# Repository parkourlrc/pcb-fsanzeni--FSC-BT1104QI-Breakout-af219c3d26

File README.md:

# Feasycom FSC-BT1104QI Breakout Board

An open-hardware breakout board designed for the Feasycom FSC-BT1104QI Bluetooth 5.4 dual-mode audio module.

This breakout board exposes the complete feature set and physical interface of the FSC-BT1104QI module. Rather than targeting standard breadboard layouts, the dual 32-pin header design breaks out all available module pins, making it an ideal core for integration into custom target boards, carrier systems, etc.

---

## Board Overview

### Front & Back Renders

| Board Front Layout | Board Rear Header Map |
| :---: | :---: |
|  |  |

---

## Key Hardware Features

- **Bluetooth Core**: Feasycom FSC-BT1104QI module supporting Bluetooth v5.4 dual-mode (Classic Bluetooth + LE Audio), preloaded with ASCII AT command modem firmware.
- **System Integration Design**: Engineered to break out all pins for clean integration onto parent/carrier PCBs.
- **USB Connectivity & Switching**: USB Type-C connector with an onboard high-bandwidth USB multiplexer (`U1`) allowing selection between direct USB communication with the Bluetooth module or serial debugging via an onboard USB-to-UART bridge.
- **Power Management**: Onboard low-noise 3.3V 600mA LDO regulator (`U3`) powering the module and peripheral logic from USB 5V.
- **Audio Routing**:
  - **Digital Audio**: Dedicated 6-pin header (`J6`) for 24-bit I2S / PCM digital audio interfaces.
  - **Analog Audio**: Dedicated 6-pin differential speaker output header (`J8`), multi-channel differential line inputs, and dual electret microphone input circuits with LC filtering.
- **Diagnostics & Testing**: Dedicated test point array (`TP1`–`TP9`) for probing power rails, reset lines, and RS-232 / UART hardware handshaking signals.

---

## Integrated Circuits

| Component Ref | Part Number | Functional Description | Key Electrical & Operating Capabilities | Datasheet Link |
| :--- | :--- | :--- | :--- | :--- |
| **U5** | **FSC-BT1104QI** | Bluetooth 5.4 Dual-Mode Audio Module (Qualcomm QCC3095 architecture, 240 MHz DSP, LE Audio, Classic BT) | - **Bluetooth Standard**: Bluetooth v5.4<br>- **Supply Voltage**: 3.3V (VDD_IO: 1.8V/3.3V)<br>- **Tx Power / Rx Sensitivity**: +10 dBm / -93 dBm<br>- **Audio Codecs**: aptX, aptX HD, aptX Adaptive, AAC, LDAC<br>- **Operating Temp**: -40°C to +85°C | [FSC-BT1104QI Datasheet](https://www.feasycom.com/product/fsc-bt1104qi/) |
| **U3** | **AP2112K-3.3** | CMOS Low Dropout (LDO) Linear Voltage Regulator | - **Input Voltage Range**: 2.5V to 6.0V<br>- **Output Voltage**: 3.3V fixed (±1.5% accuracy)<br>- **Max Output Current**: 600 mA<br>- **Dropout Voltage**: 250 mV typical at 600 mA<br>- **Features**: Enable control, current limit, thermal shutdown | [AP2112K-3.3 Datasheet](https://www.diodes.com/assets/Datasheets/AP2112.pdf) |
| **U4** | **CH340G** | USB to Serial / UART Interface Bridge Transceiver | - **USB Interface**: USB 2.0 Full-Speed compliant<br>- **Baud Rates**: 50 bps to 2 Mbps<br>- **Supply Voltage**: 3.3V or 5.0V operation<br>- **Signals**: Full modem signals (RTS, CTS, DTR, DSR, RI, DCD) | [CH340G Datasheet](https://cdn.sparkfun.com/datasheets/Dev/Arduino/Other/CH340DS1.PDF) |
| **U1** | **TS3USB30EDGSR** | High-Speed USB 2.0 (480 Mbps) 1:2 Multiplexer / Switch | - **Supply Voltage Range**: 1.8V to 4.3V<br>- **Bandwidth**: 900 MHz (-3 dB bandwidth)<br>- **ON-State Resistance**: 4.5 Ω typical<br>- **ESD Protection**: 8 kV HBM ESD performance | [TS3USB30EDGSR Datasheet](https://www.ti.com/product/TS3USB30E/part-details/TS3USB30EDGSR) |

---

## Pinout Definitions & Interface Maps

### 1. Right Header Connector `P1`

---

### 2. Left Header Connector `P2`

---

### 3. Digital Audio Header `J6` (I2S Connector)

---

### 4. Differential Speaker Header `J8`

---

### 5. Onboard Diagnostic Test Points (`TP1`–`TP9`)

---

## Jumpers & Configuration Switches

- **`J1` (`USB_SEL`)**:
  - **Bridge 1-2**: Route USB Type-C lines to **CH340G** USB-to-UART bridge.
  - **Bridge 2-3**: Route USB Type-C lines directly to the **FSC-BT1104QI** module.
- **`JP1` (`ENABLE`)**: Disconnect if feeding 3.3V from P1 or P2.
- **`SW1` (`POWER_ON` / `SYS_CTRL`)**: Momentary push button tied to `SYS_CTRL` (Pin 2 on FSC module) for powering on/off or waking the module from sleep modes.

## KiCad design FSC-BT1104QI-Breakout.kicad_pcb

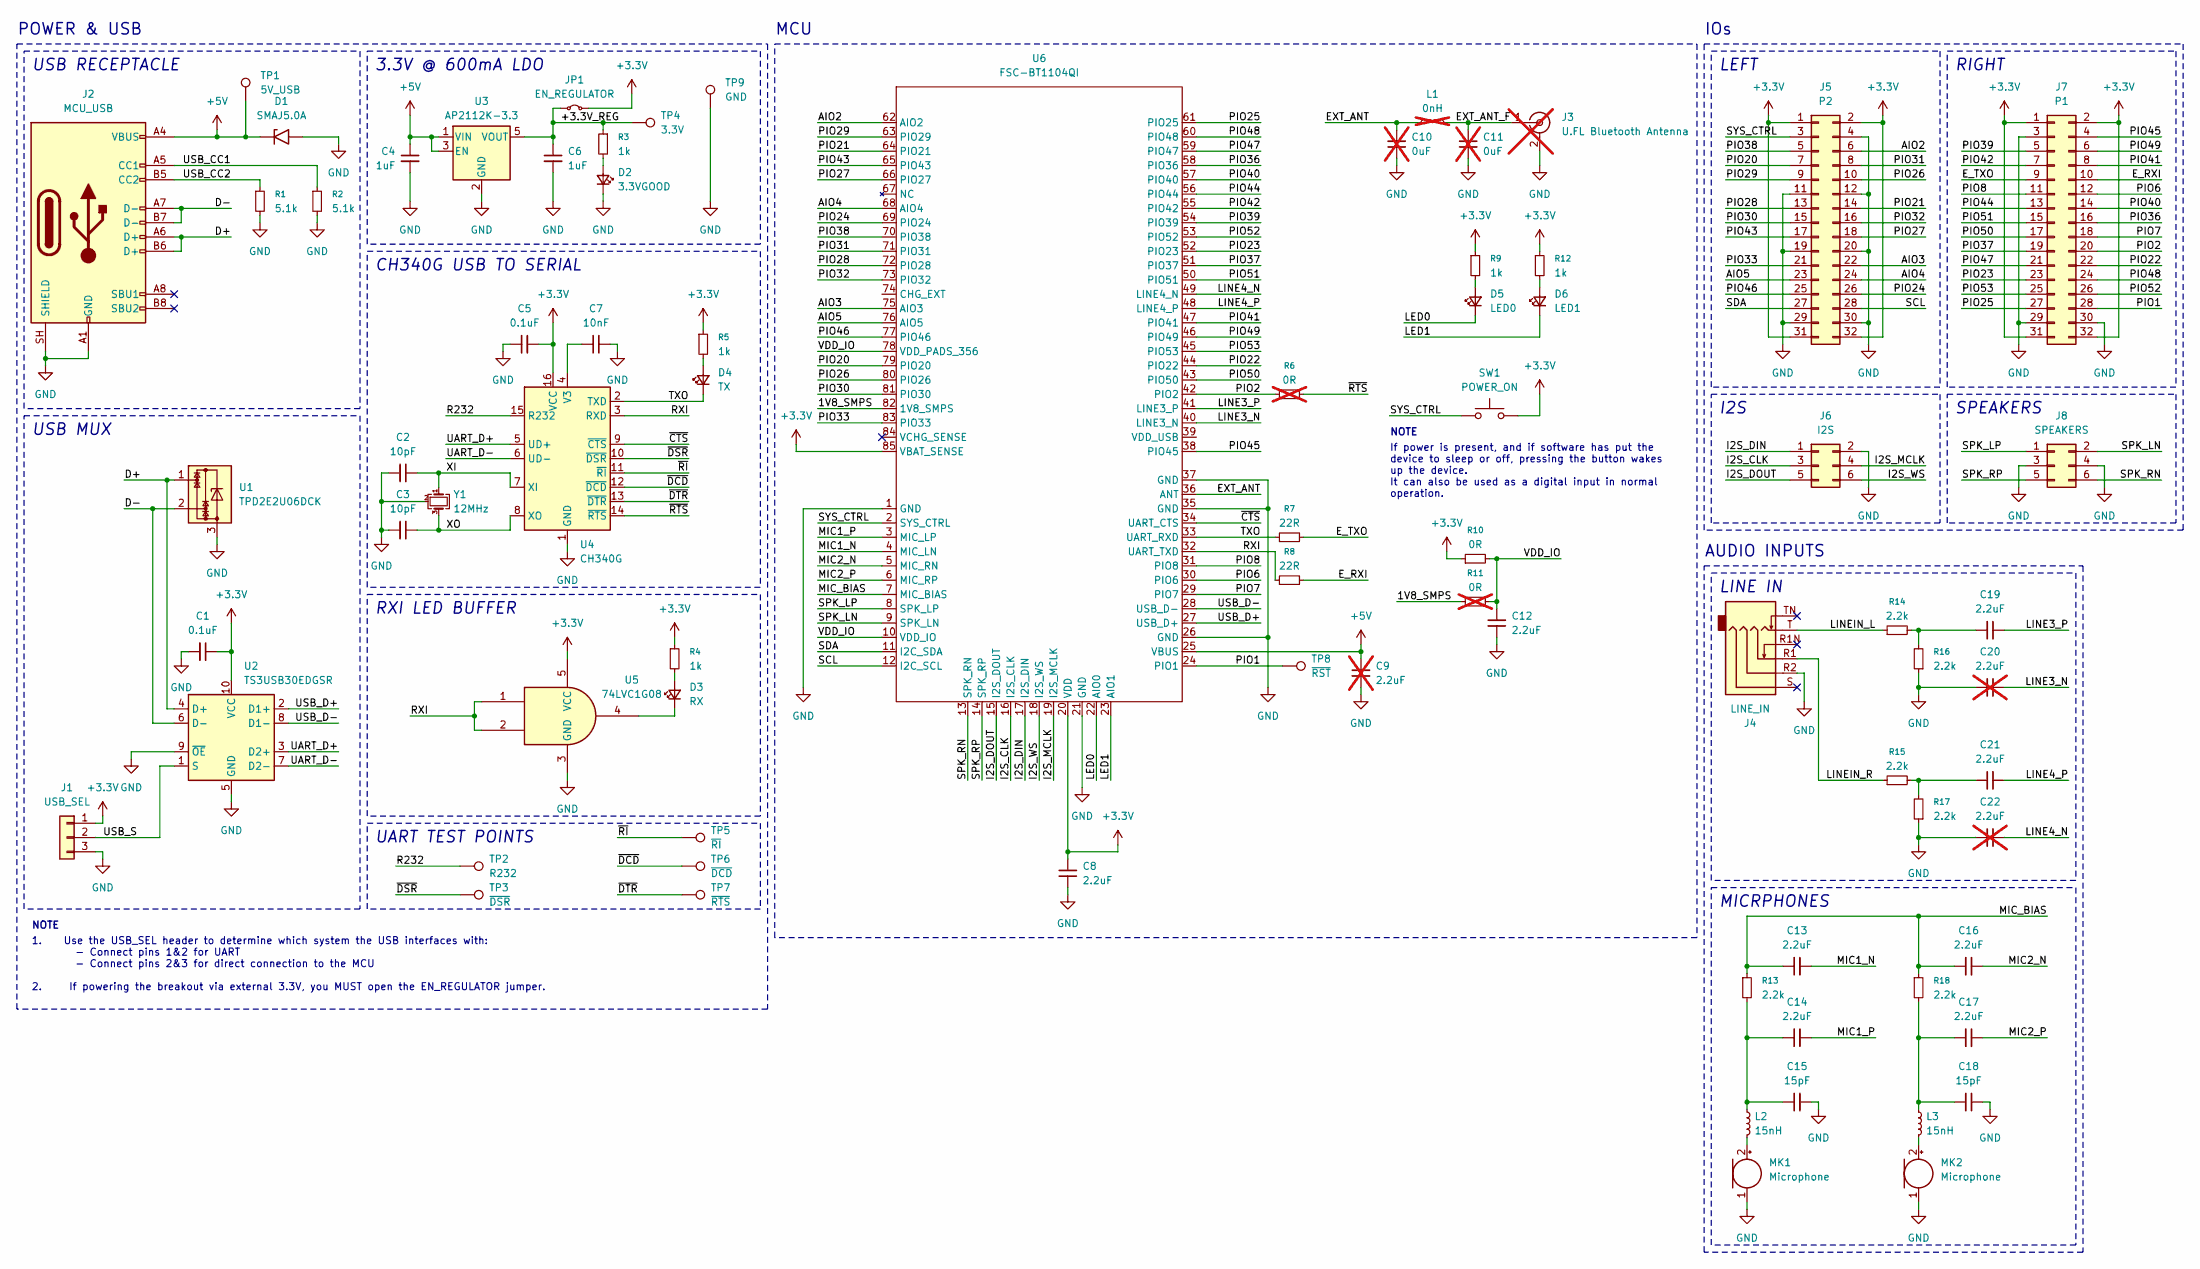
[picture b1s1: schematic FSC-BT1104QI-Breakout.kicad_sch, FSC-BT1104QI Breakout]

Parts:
C1, C5: 0.1uF; C_0603_1608Metric
C2, C3: 10pF; C_0603_1608Metric
C4, C6: 1uF; C_0805_2012Metric
C7: 10nF; C_0603_1608Metric
C8, C12, C13, C14, C16, C17, C19, C21: 2.2uF; C_0603_1608Metric
C9, C20, C22: 2.2uF; C_0603_1608Metric; not fitted
C10, C11: 0uF; C_0603_1608Metric; not fitted
C15, C18: 15pF; C_0603_1608Metric
D1: SMAJ5.0A; D_SMA
D2: 3.3VGOOD; LED_0603_1608Metric
D3: RX; LED_0603_1608Metric
D4: TX; LED_0603_1608Metric
D5: LED0; LED_0603_1608Metric
D6: LED1; LED_0603_1608Metric
J1: USB_SEL; PinHeader_1x03_P2.54mm_Vertical
J2: MCU_USB; SHOUHAN_TYPE-C_16PIN_2MD__073
J3: U.FL Bluetooth Antenna; U.FL_Molex_MCRF_73412-0110_Vertical; not fitted
J4: LINE_IN; Jack_3.5mm_PJ31060-I_Horizontal
J5: P2; PinHeader_2x16_P2.54mm_Vertical
J6: I2S; PinHeader_2x03_P2.54mm_Vertical
J7: P1; PinHeader_2x16_P2.54mm_Vertical
J8: SPEAKERS; PinHeader_2x03_P2.54mm_Vertical
JP1: EN_REGULATOR; PinHeader_1x02_P2.54mm_Vertical
L1: 0nH; L_0603_1608Metric; not fitted
L2, L3: 15nH; L_0603_1608Metric
MK1, MK2: Microphone; GMI4015P-2C-42db
R1, R2: 5.1k; R_0603_1608Metric
R3, R4, R5, R9, R12: 1k; R_0603_1608Metric
R6, R11: 0R; R_0603_1608Metric; not fitted
R7, R8: 22R; R_0603_1608Metric
R10: 0R; R_0603_1608Metric
R13, R14, R15, R16, R17, R18: 2.2k; R_0603_1608Metric
SW1: POWER_ON; SW_Push_1P1T_NO_CK_KMR2
TP1: 5V_USB; TestPoint_Pad_D1.5mm
TP2: R232; TestPoint_Pad_D1.5mm
TP3: ~{DSR}; TestPoint_Pad_D1.5mm
TP4: 3.3V; TestPoint_Pad_D1.5mm
TP5: ~{RI}; TestPoint_Pad_D1.5mm
TP6: ~{DCD}; TestPoint_Pad_D1.5mm
TP7: ~{RTS}; TestPoint_Pad_D1.5mm
TP8: ~{RST}; TestPoint_Pad_D1.5mm
TP9: GND; TestPoint_Pad_D1.5mm
U1: TPD2E2U06DCK; SOT-323_SC-70
U2: TS3USB30EDGSR; TSSOP-10_3x3mm_P0.5mm
U3: AP2112K-3.3; SOT-23-5
U4: CH340G; SOIC-16_3.9x9.9mm_P1.27mm
U5: 74LVC1G08; SOT-23-5
U6: FSC-BT1104QI
Y1: 12MHz; TAXM12M4RLBDDT2T

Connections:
+3.3V: C1.2, C5.2, C8.2, J1.1, J5.1, J5.2, J5.31, J5.32, J7.1, J7.2, J7.31, J7.32, JP1.2 (B), R4.1, R5.1, R9.1, R10.1, R12.1, SW1.2, U2.10 (VCC), U4.16 (VCC), U5.5 (VCC), U6.20 (VDD), U6.85 (VBAT_SENSE)
+5V: C4.1, C9.2, D1.1 (A1), J2.A4 (VBUS), J2.A9 (VBUS), J2.B4 (VBUS), J2.B9 (VBUS), TP1.1 (1_1), U3.1 (VIN), U3.3 (EN), U6.25 (VBUS)
/1V8_SMPS: R11.1, U6.82 (1V8_SMPS)
/+3.3V_REG: C6.1, JP1.1 (A), R3.1, TP4.1 (1_1), U3.5 (VOUT)
/AIO2: J5.6, U6.62 (AIO2)
/AIO3: J5.22, U6.75 (AIO3)
/AIO4: J5.24, U6.68 (AIO4)
/AIO5: J5.23, U6.76 (AIO5)
/D+: J2.A6 (D+), J2.B6 (D+), U1.1, U2.4 (D+)
/D-: J2.A7 (D-), J2.B7 (D-), U1.2, U2.6 (D-)
/EXT_ANT: C10.2, L1.1, U6.36 (ANT)
/EXT_ANT_F: C11.2, J3.1 (In), L1.2
/E_RXI: J7.10, R8.2
/E_TXO: J7.9, R7.2
/I2S_CLK: J6.3, U6.16 (I2S_CLK)
/I2S_DIN: J6.1, U6.17 (I2S_DIN)
/I2S_DOUT: J6.5, U6.15 (I2S_DOUT)
/I2S_MCLK: J6.4, U6.19 (I2S_MCLK)
/I2S_WS: J6.6, U6.18 (I2S_WS)
/LED0: D5.1 (K), U6.22 (AIO0)
/LED1: D6.1 (K), U6.23 (AIO1)
/LINE3_N: C20.2, U6.40 (LINE3_N)
/LINE3_P: C19.2, U6.41 (LINE3_P)
/LINE4_N: C22.2, U6.49 (LINE4_N)
/LINE4_P: C21.2, U6.48 (LINE4_P)
/LINEIN_L: J4.T, R14.1
/LINEIN_R: J4.R1, R15.1
/MIC1_N: C13.2, U6.4 (MIC_LN)
/MIC1_P: C14.2, U6.3 (MIC_LP)
/MIC2_N: C16.2, U6.5 (MIC_RN)
/MIC2_P: C17.2, U6.6 (MIC_RP)
/MIC_BIAS: C13.1, C16.1, R13.1, R18.1, U6.7 (MIC_BIAS)
/PIO1: J7.28, TP8.1 (1_1), U6.24 (PIO1)
/PIO2: J7.20, R6.1, U6.42 (PIO2)
/PIO6: J7.12, U6.30 (PIO6)
/PIO7: J7.18, U6.29 (PIO7)
/PIO8: J7.11, U6.31 (PIO8)
/PIO20: J5.7, U6.79 (PIO20)
/PIO21: J5.14, U6.64 (PIO21)
/PIO22: J7.22, U6.44 (PIO22)
/PIO23: J7.23, U6.52 (PIO23)
/PIO24: J5.26, U6.69 (PIO24)
/PIO25: J7.27, U6.61 (PIO25)
/PIO26: J5.10, U6.80 (PIO26)
/PIO27: J5.18, U6.66 (PIO27)
/PIO28: J5.13, U6.72 (PIO28)
/PIO29: J5.9, U6.63 (PIO29)
/PIO30: J5.15, U6.81 (PIO30)
/PIO31: J5.8, U6.71 (PIO31)
/PIO32: J5.16, U6.73 (PIO32)
/PIO33: J5.21, U6.83 (PIO33)
/PIO36: J7.16, U6.58 (PIO36)
/PIO37: J7.19, U6.51 (PIO37)
/PIO38: J5.5, U6.70 (PIO38)
/PIO39: J7.5, U6.54 (PIO39)
/PIO40: J7.14, U6.57 (PIO40)
/PIO41: J7.8, U6.47 (PIO41)
/PIO42: J7.7, U6.55 (PIO42)
/PIO43: J5.17, U6.65 (PIO43)
/PIO44: J7.13, U6.56 (PIO44)
/PIO45: J7.4, U6.38 (PIO45)
/PIO46: J5.25, U6.77 (PIO46)
/PIO47: J7.21, U6.59 (PIO47)
/PIO48: J7.24, U6.60 (PIO48)
/PIO49: J7.6, U6.46 (PIO49)
/PIO50: J7.17, U6.43 (PIO50)
/PIO51: J7.15, U6.50 (PIO51)
/PIO52: J7.26, U6.53 (PIO52)
/PIO53: J7.25, U6.45 (PIO53)
/R232: TP2.1 (1_1), U4.15 (R232)
/RXI: R8.1, U4.3 (RXD), U5.1, U5.2, U6.32 (UART_TXD)
/SCL: J5.28, U6.12 (I2C_SCL)
/SDA: J5.27, U6.11 (I2C_SDA)
/SPK_LN: J8.2, U6.9 (SPK_LN)
/SPK_LP: J8.1, U6.8 (SPK_LP)
/SPK_RN: J8.6, U6.13 (SPK_RN)
/SPK_RP: J8.5, U6.14 (SPK_RP)
/SYS_CTRL: J5.3, SW1.1, U6.2 (SYS_CTRL)
/TXO: D4.1 (K), R7.1, U4.2 (TXD), U6.33 (UART_RXD)
/UART_D+: U2.3 (D2+), U4.5 (UD+)
/UART_D-: U2.7 (D2-), U4.6 (UD-)
/USB_CC1: J2.A5 (CC1), R2.1
/USB_CC2: J2.B5 (CC2), R1.1
/USB_D+: U2.2 (D1+), U6.27 (USB_D+)
/USB_D-: U2.8 (D1-), U6.28 (USB_D-)
/USB_S: J1.2, U2.1 (S)
/VDD_IO: C12.1, R10.2, R11.2, U6.10 (VDD_IO), U6.78 (VDD_PADS_356)
/XI: C2.2, U4.7 (XI), Y1.1
/XO: C3.2, U4.8 (XO), Y1.3
/~CTS: U4.9 (~CTS), U6.34 (UART_CTS)
/~DCD: TP6.1 (1_1), U4.12 (~DCD)
/~DSR: TP3.1 (1_1), U4.10 (~DSR)
/~DTR: TP7.1 (1_1), U4.13 (~DTR)
/~RI: TP5.1 (1_1), U4.11 (~RI)
/~RTS: R6.2, U4.14 (~RTS)
GND: C1.1, C2.1, C3.1, C4.2, C5.1, C6.2, C7.2, C8.1, C9.1, C10.1, C11.1, C12.2, C15.2, C18.2, C20.1, C22.1, D1.2 (A2), D2.1 (K), J1.3, J2.A1 (GND), J2.A12 (GND), J2.B1 (GND), J2.B12 (GND), J2.SH (SHIELD), J3.2 (Ext), J4.R2, J5.4, J5.11, J5.12, J5.19, J5.20, J5.29, J5.30, J6.2, J7.3, J7.29, J7.30, J8.3, J8.4, MK1.1 (-), MK2.1 (-), R1.2, R2.2, R16.1, R17.1, TP9.1 (1_1), U1.3, U2.5 (GND), U2.9 (~OE), U3.2 (GND), U4.1 (GND), U5.3 (GND), U6.1 (GND), U6.21 (GND), U6.26 (GND), U6.35 (GND), U6.37 (GND), Y1.2 (G), Y1.4 (G)
unnamed: C14.1, C15.1, L2.1, R13.2
unnamed: C17.1, C18.1, L3.1, R18.2
unnamed: C19.1, R14.2, R16.2
unnamed: C21.1, R15.2, R17.2
unnamed: D2.2 (A), R3.2
unnamed: D3.2 (A), R4.2
unnamed: D3.1 (K), U5.4
unnamed: D4.2 (A), R5.2
unnamed: D5.2 (A), R9.2
unnamed: D6.2 (A), R12.2
unnamed: L2.2, MK1.2 (+)
unnamed: L3.2, MK2.2 (+)
unnamed: C7.1, U4.4 (V3)

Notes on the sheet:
MICRPHONES
UART TEST POINTS
IOs
LEFT
I2S
LINE IN
RIGHT
NOTE
MCU
CH340G USB TO SERIAL
POWER & USB
3.3V @ 600mA LDO
1. Use the USB_SEL header to determine which system the USB interfaces with: - Connect pins 1&2 for UART - Connect pins 2&3 for direct connection to the MCU 2. If powering the breakout via external 3.3V, you MUST open the EN_REGULATOR jumper.
USB RECEPTACLE
USB MUX
AUDIO INPUTS
RXI LED BUFFER
SPEAKERS
If power is present, and if software has put the device to sleep or off, pressing the button wakes up the device. It can also be used as a digital input in normal operation.

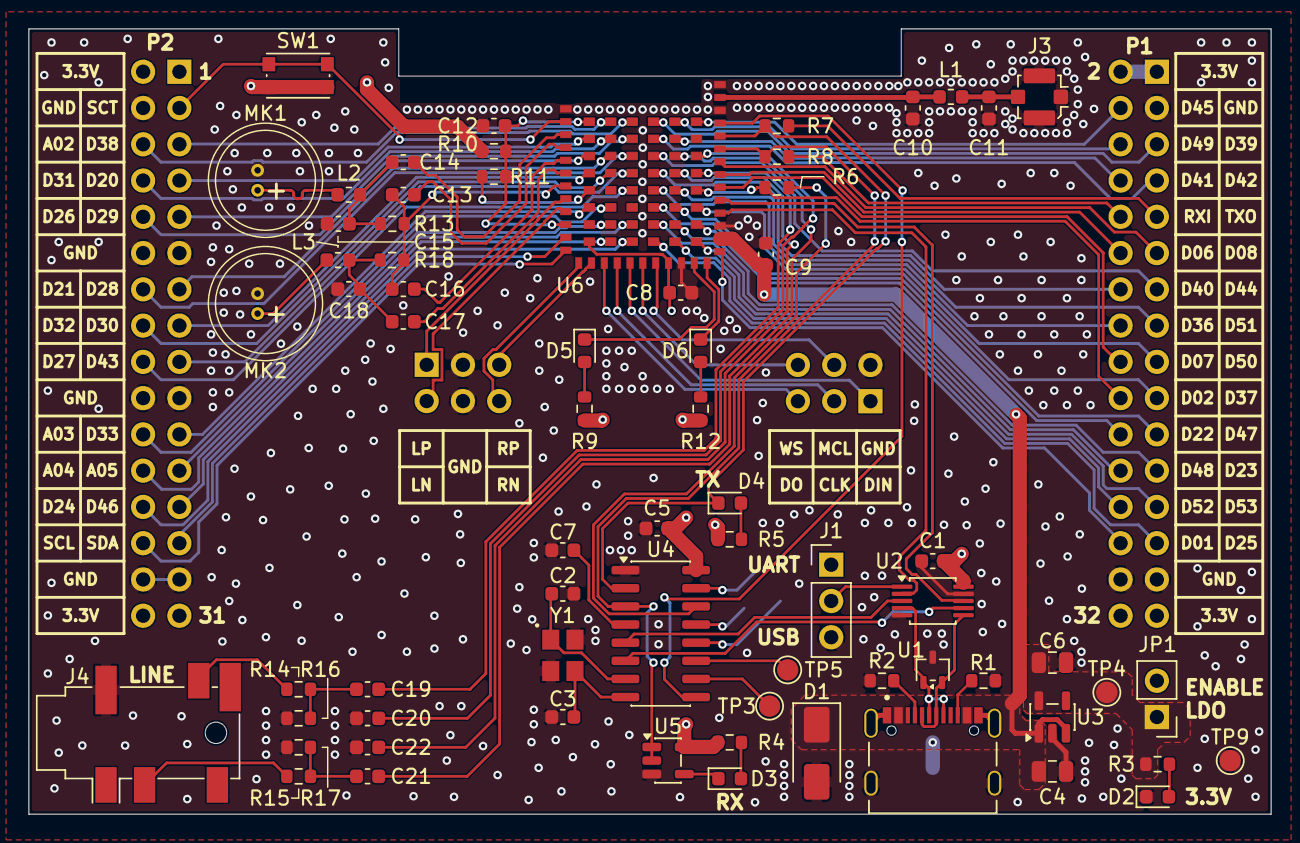
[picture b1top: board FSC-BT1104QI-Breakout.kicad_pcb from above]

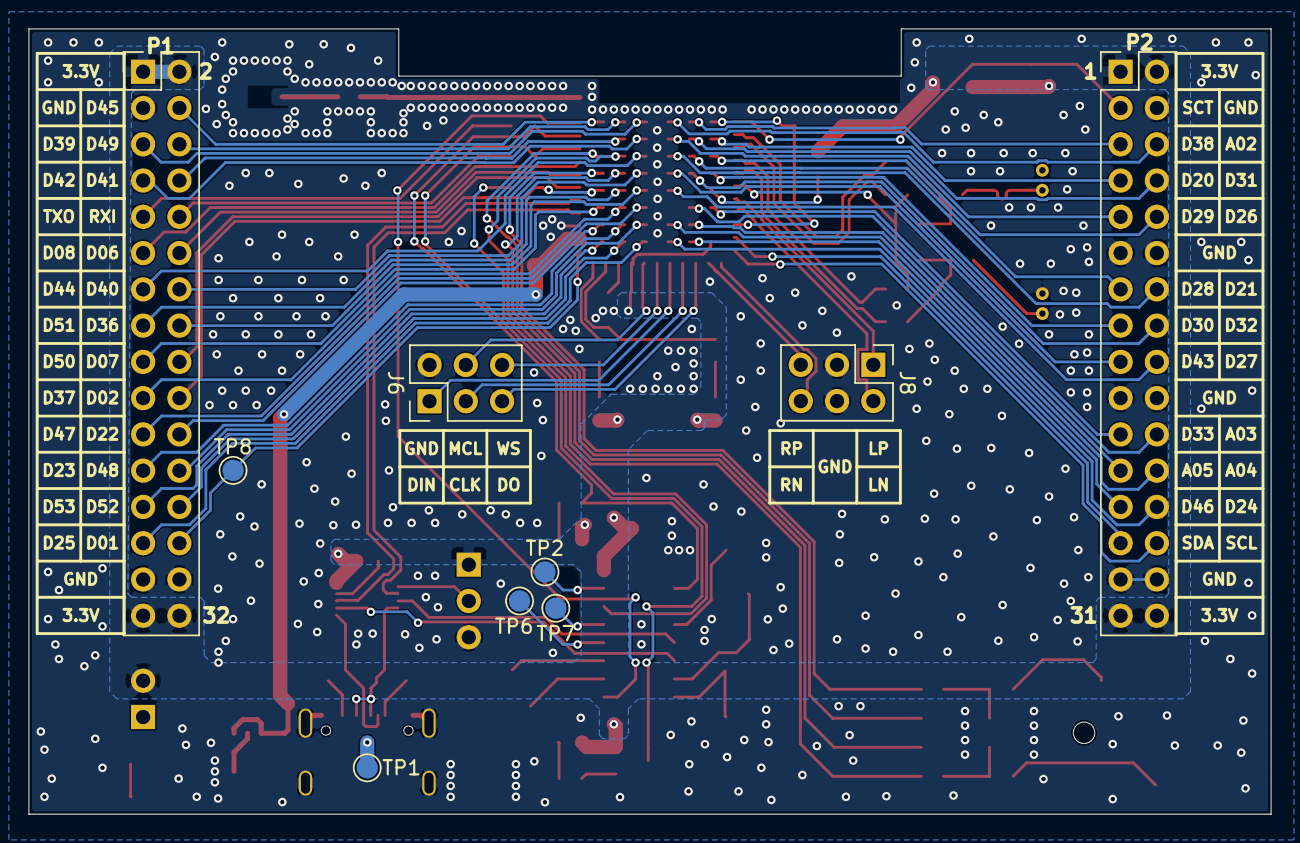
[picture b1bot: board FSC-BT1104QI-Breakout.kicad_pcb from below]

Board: 4 copper layers, 87.0 x 55.0 mm, 77 parts (9 on the bottom side), 109 nets.
